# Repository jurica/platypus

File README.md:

# platypus keyboards

This is a work in progress set of ultra low profile keyboards for the Kailh PG1316S switches.

## variants
### split
The first keyboard in the series. 36 keys split design, using the Seeed Xiao NRF53840 MCU.

### uni
tbd...

## references
 - https://grabcad.com/library/seeed-studio-xiao-nrf52840-sense-1
 - https://github.com/mikeholscher/zmk-config-mikefive
 - https://github.com/joe-scotto/scottokeebs
 - https://discord.com/channels/719497620560543766/914245039222292501/914686996096614450

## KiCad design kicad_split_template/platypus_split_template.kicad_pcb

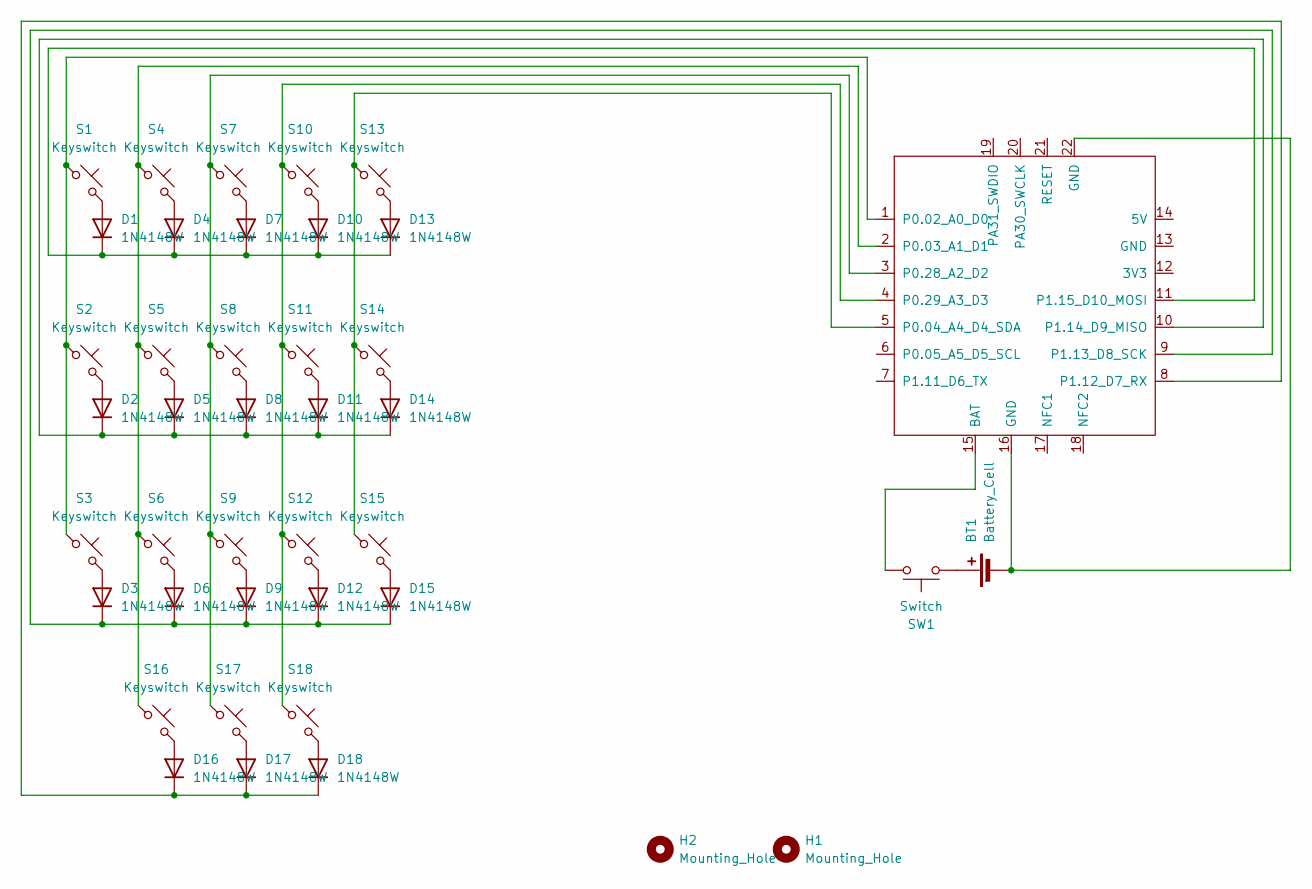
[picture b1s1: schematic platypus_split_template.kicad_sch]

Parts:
BT1: Battery_Cell; SolderWire-0.5sqmm_1x02_P4.6mm_D0.9mm_OD2.1mm
D1, D2, D3, D4, D5, D6, D7, D8, D9, D10, D11, D12, D13, D14, D15, D16, D17, D18: 1N4148W; D_SOD-123
H1, H2: Mounting_Hole; Standoff_M2x6mm
S1, S2, S3, S4, S5, S6, S7, S8, S9, S10, S11, S12, S13, S14, S15, S16, S17, S18: Keyswitch; CPG1316S01D02_mikeholscher
SW1: Switch; Switch_MSK12C02
U2: XIAO-nRF52840-SMD

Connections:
unnamed: BT1.1 (+), SW1.1
unnamed: BT1.2 (-), U2.16 (GND), U2.22 (GND)
unnamed: D1.2 (A), S1.2
unnamed: D1.1 (K), D4.1 (K), D7.1 (K), D10.1 (K), D13.1 (K), U2.11 (P1.15_D10_MOSI)
unnamed: D2.2 (A), S2.2
unnamed: D3.2 (A), S3.2
unnamed: D4.2 (A), S4.2
unnamed: D5.2 (A), S5.2
unnamed: D6.2 (A), S6.2
unnamed: D7.2 (A), S7.2
unnamed: D8.2 (A), S8.2
unnamed: D9.2 (A), S9.2
unnamed: D10.2 (A), S10.2
unnamed: D11.2 (A), S11.2
unnamed: D2.1 (K), D5.1 (K), D8.1 (K), D11.1 (K), D14.1 (K), U2.10 (P1.14_D9_MISO)
unnamed: D12.2 (A), S12.2
unnamed: D3.1 (K), D6.1 (K), D9.1 (K), D12.1 (K), D15.1 (K), U2.9 (P1.13_D8_SCK)
unnamed: D13.2 (A), S13.2
unnamed: D14.2 (A), S14.2
unnamed: D15.2 (A), S15.2
unnamed: D16.2 (A), S16.2
unnamed: D16.1 (K), D17.1 (K), D18.1 (K), U2.8 (P1.12_D7_RX)
unnamed: D17.2 (A), S17.2
unnamed: D18.2 (A), S18.2
unnamed: SW1.2, U2.15 (BAT)
unnamed: S1.1, S2.1, S3.1, U2.1 (P0.02_A0_D0)
unnamed: S4.1, S5.1, S6.1, S16.1, U2.2 (P0.03_A1_D1)
unnamed: S13.1, S14.1, S15.1, U2.5 (P0.04_A4_D4_SDA)
unnamed: S7.1, S8.1, S9.1, S17.1, U2.3 (P0.28_A2_D2)
unnamed: S10.1, S11.1, S12.1, S18.1, U2.4 (P0.29_A3_D3)

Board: 2 copper layers, 41 parts (0 on the bottom side), 30 nets, no tracks yet.

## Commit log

2024-12-29 init
